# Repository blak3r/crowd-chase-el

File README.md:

## Crowd Chase EL

Is a simple EL wire controller to be used by a group of people wearing EL Wires.
Each person sets which number they are in a sequence by pressing a push button.  They also set the total number of people in their
group using the other push button.  So, if you had 3 people.  Someone would be 1 of 3, 2 of 3, and 3 of 3.

The controller then turns on their EL Wire whenever it's their turn in the sequence.

The circuit uses a basic 8 bit PIC microcontroller (sorry arduino peeps)... The board design uses all through hole components to make it easy for novices to solder.

I designed this controller for Burning Man 2013.  We all invested in some EL Wire (for safety reasons)... and thought it'd be
really cool if we blinked in succession.  Plus it'd had been a while since I had done a hardware project.

### Quick Info ###
* BOM Cost: $8.60 in Qty 10 (not including the PCBs)
* Compiler: Microchip XC8 (but any compiler for PIC16 should be fine)
* PCB Layout: Eagle v6
* License: Creative Commons Share a Like
* Microcontroller: PIC16F1826
* IDE used: MPLABX
* Battery Life: Over a week on a single CR2032.

## Where's the source code? ##
If I haven't posted it here yet, just shoot me an email (see github profile).  I reused a project that I have to strip some of the files
out of before I can release it as open source.

### Project Status ###
I'm looking for people who want to take this project to the next level.  I started this as a project for burning man 2013.
I got it to work but there are some improvements that could be made.

__I'd be willing to ship out some of the controller boards I made to someone that would like to continue this project.__

### Version 1 ###

Well, I made quite a few mistakes on the version 1 board which i'll outline here.  I had very little time to get this board
out before my deadline.  The board works it just required assembling things slightly different and in soldering a resistor
here and there to another part because there wasn't a pad.

1. I should have used optically isolated triacs!  You have to use a optically isolated triacs when you're using battery powered circuits.  Basically, you should just always
use optotriac's unless you are certain you don't need them.  If you don't, then you don't have a common ground reference between
the AC output of the inverter and the battery powered controller pcb.  This was a pretty embarrassing mistake.  I was pretty
confused how it was going to work in the first place and shouldn't have just "trusted" that the SparkFun design would work in
my situation.  The sparkfun board basically assumes that you will be powering your inverter and your controller board off one or
more DC wall worts, which in general, will share a common ground (your earth ground of your house)...

I came up with a fairly clever workaround... based around parts I had laying around.  I had some N-channel and p-channel mosfets that worked out.  I got lucky
as I added pads for a second TO-92 transistor along with .1" header to act as a breakout.  So, what I ended up doing is rather then switching the AC voltage from the invertor,
I switched the battery voltage for the inverter using a load switch.  I think this approach is actually probably better anyway as with some invertors
it's bad to keep them running without any load (ie EL Wire) connected to them.

2. The schematic has a PIC18F part on it but the target is actually a PIC16F chip.  I used an 18 pin microchip library that was in the sparkfun library but the pins
don't match 100%... so the IO pins used in the source code don't match the IO pin numbers on the schematic.

3. I forgot to put pull ups on one of the switches and it was connected to an PORTA io pin which can't have weak pullups enabled :(.

4. The voltage regulator pins didn't match the one I used in the library.  As a result you have to rotate the part slightly
 when assembling.

5. My 1.8V regulated output is NOT enough for the LEDs i picked.  The LEDs don't blink very brightly which makes
it really annoying to work with outdoors when the sun is up.

6. Some of the boards are a bit unreliable.  I found the PIC going into failsafe oscillator mode from time to time.  I'm not sure
exactly what the cause of this is... Perhaps the crystals are finicky to loading... perhaps it's the 1.8V operating voltage...
perhaps it's the fact that my boards didn't have solder mask on them and I never completely potted the boards as I ran out of
time and things shorted out.  I'd definitely recommend getting solder mask!

7. My ICSP pads for the Tag Connect didn't seem to work.  I suspect this was due to the limited number of drill sizes
that PCBExpress offers on their standard service.  The holes for the line up pins were WAY to large.  As a result, I ended up

### Other Critiques ###

1. The board could be a LOT smaller... I decided to go through-hole to make the part very easy to assemble... but it really adds a lot of bulk.
2. I wasn't very happy with the push buttons.  They take up quite a bit of board space.  I'd also like to see a switch with recessed actuators to prevent
the possibility of being pressed accidently in pocket.  Note: this didn't actually happen to us in practice... probably because of the bulky
connectors on the edges of the board.
3. Syncing is a bit difficult unless you have a group of patient people.  There were two ways to sync A) by everyone releasing a button at the same time and B) by connecting the boards
together with two wires.  The pressing a button can be difficult with a lot of people... It's hard to have everyone release the button "on 3". 1-2-3.
The wire method is also difficult when you have people who have already put their costumes on etc.

### Alternate Sync Methods ###

The way I kept the boards in sync was just by using timers in the micro and having them "reset" when the sync action occurs.  This works fairly well for
an evening or two.  Depending on where you're using it that might not be an issue.  But, getting 7 people together at Burning Man is pretty much
impossible and if you do you'll run into the issue mentioned above.  To improve the accuracy of the clocks, I used what I thought was a fairly
precise crystal and used an LDO on board to eliminate changes in the operating voltage from PIC to PIC.

What would be ideal is some sort of low power zigbee node mesh controller... where master and slaves are dynamically negotiated.  The master would then send
out a pulse signal to the slave nodes when it was their turn.  This would make the whole thing much easier to use as a group.
As people come in range they'd be assigned a position automatically.
If two people went off on their own, then they'd start blinking back and forth instead of having dead time where neither is blinking.
It would however make for some pretty complex software and increase the BOM Cost probably about $5-$10.  The possibilities
would be pretty much endless though... You could probably even do some smart algorithms to determine where people were in relation to one another.
That way you could always keep the blink pattern going from left to right even when people moved around.

A simpler approach would be a simple RF transmitter / receiver pairs.  In this topology you'd have a single master controller which would send
pulse signals to the slave boards to keep them in sync.  You can get these for about $5 but what I didn't like about that was then you
always had to have a "master" board in range of the "slave" board and they'd drain the coin cell batteries pretty fast.  The zigbee stacks have battery
friendly "time slots" in which all communications occur so the RF controllers could be off most of the time.

### Contact ####
I'm very interested in seeing this project go somewhere.  I'm afraid I don't have too much time to keep working on it nor an event
to use it at for at least a year... so send me an email if you're interested.  My email is in my github profile.

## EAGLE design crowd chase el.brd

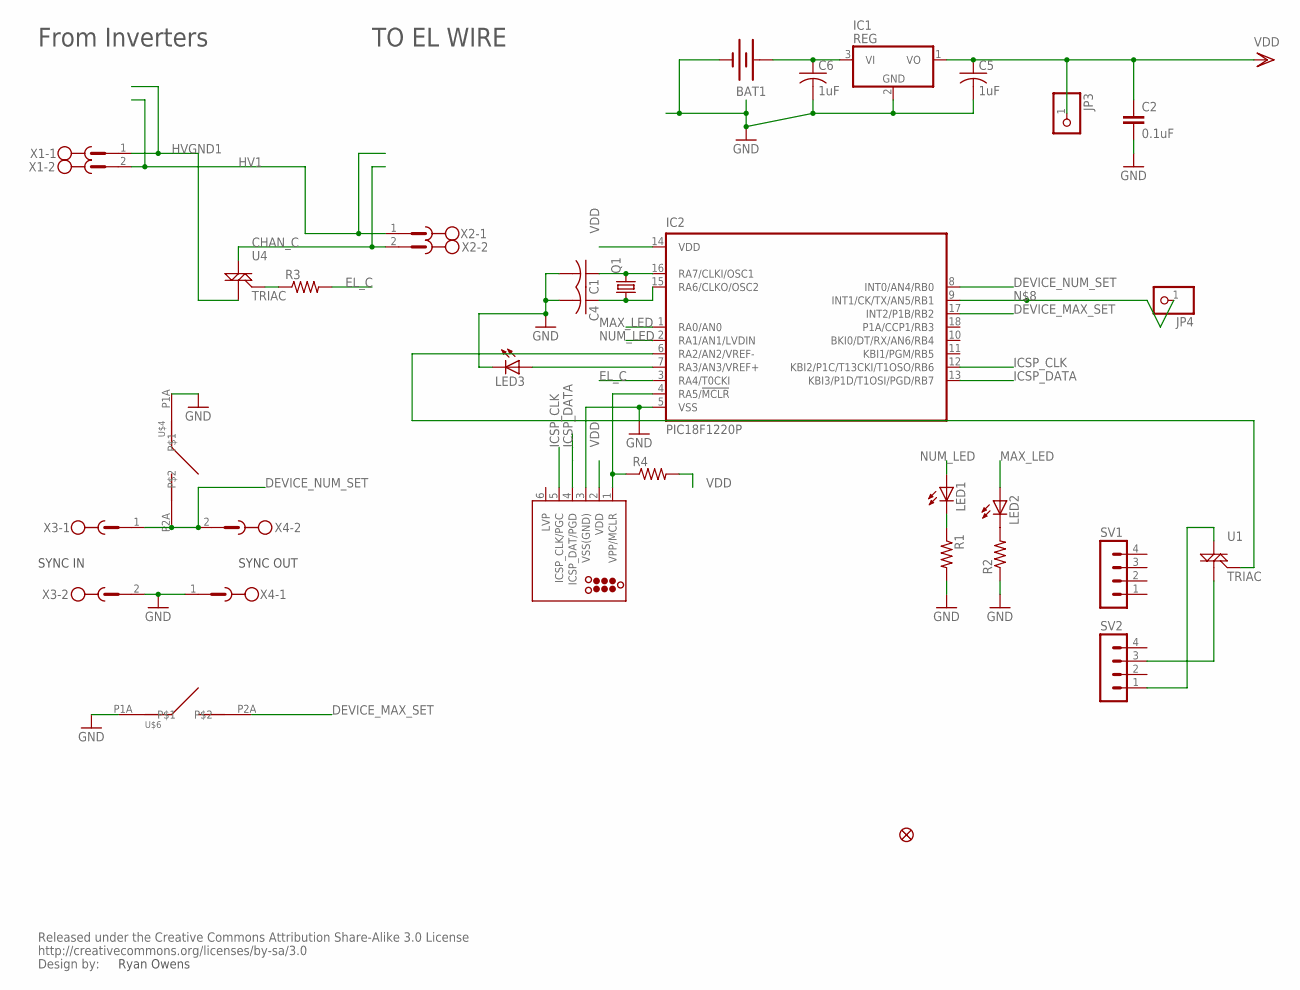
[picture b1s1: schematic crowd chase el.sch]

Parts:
BAT1: BATTERY20SMD-L; BATTCON_20MM
C1, C4: C-US025-025X050; C025-025X050
C2: 0.1uF; CAP-PTH-SMALL2
C5, C6: 1uF; C025-025X050
IC1: REG; TO92
IC2: PIC18F1220P; DIL18
J2: TC2030; TC2030-MCP-NL-CP
JP3, JP4: PINHEADER_1X1; HEADER_DIP_1X01
LED1, LED2, LED3: LED3MM
Q1: CRYSTALHC49S; HC49/S
R1, R2, R3, R4: R-US_0204/5; 0204/5
SV1, SV2: MA04-1
U1, U4: TRIAC; TO-92
U$2: FIDUCIAL1X2; FIDUCIAL-1X2
U$4, U$6: 12MMTACT_MJTP1212; MJTP1212
U$5: CREATIVE_COMMONS
X1, X2, X3, X4: MSTBV2

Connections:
CHAN_C: U4.3 (M2), X2.2
DEVICE_MAX_SET: IC2.17 (INT2/P1B/RB2), U$6.P2A
DEVICE_NUM_SET: IC2.8 (INT0/AN4/RB0), U$4.P2A, X3.1, X4.2
EL_C: IC2.3 (RA4/T0CKI), R3.2
GND: BAT1.2 (-), C1.2, C2.2, C4.2, C5.2, C6.2, IC1.2 (GND), IC2.5 (VSS), J2.3 (VSS(GND)), LED3.K (C), R1.2, R2.1, U$4.P1A, U$6.P1A, X3.2, X4.1
HV1: X1.2, X2.1
HVGND1: U4.1 (M1), X1.1
ICSP_CLK: IC2.12 (KBI2/P1C/T13CKI/T1OSO/RB6), J2.5 (ICSP_CLK/PGC)
ICSP_DATA: IC2.13 (KBI3/P1D/T1OSI/PGD/RB7), J2.4 (ICSP_DAT/PGD)
MAX_LED: IC2.1 (RA0/AN0), LED2.A
unnamed: IC2.4 (RA5/!MCLR), J2.1 (VPP/MCLR), R4.1
unnamed: C4.1, IC2.15 (RA6/CLKO/OSC2), Q1.1
unnamed: C1.1, IC2.16 (RA7/CLKI/OSC1), Q1.2
unnamed: LED1.K (C), R1.1
unnamed: LED2.K (C), R2.2
unnamed: IC2.7 (RA3/AN3/VREF+), LED3.A
unnamed: IC2.9 (INT1/CK/TX/AN5/RB1), JP4.1
unnamed: BAT1.3 (+), C6.1, IC1.3 (VI)
unnamed: R3.1, U4.2 (G)
unnamed: SV2.1, U1.3 (M2)
unnamed: SV2.3, U1.1 (M1)
unnamed: IC2.6 (RA2/AN2/VREF-), U1.2 (G)
NUM_LED: IC2.2 (RA1/AN1/LVDIN), LED1.A
VDD: C2.1, C5.1, IC1.1 (VO), IC2.14 (VDD), J2.2 (VDD), JP3.1, R4.2

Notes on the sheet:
Ryan Owens
TO EL WIRE
From Inverters
SYNC OUT
SYNC IN

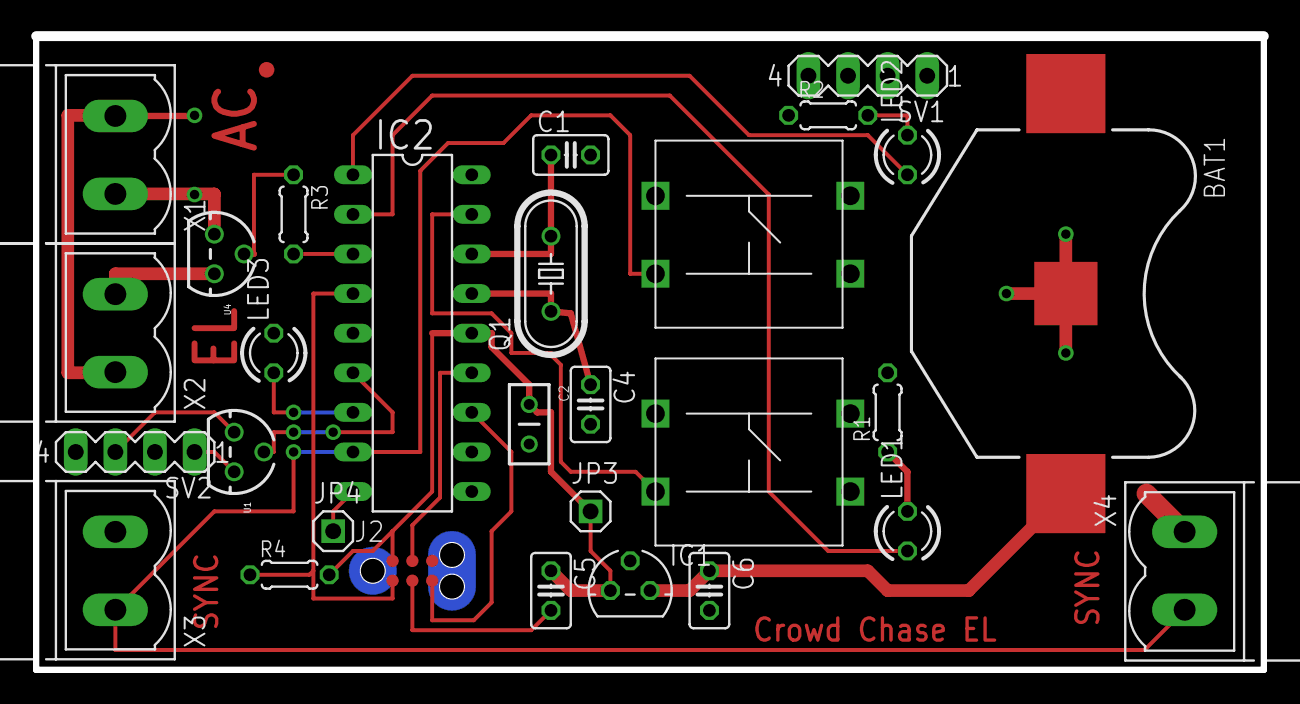
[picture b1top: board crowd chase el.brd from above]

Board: 2 copper layers, 78.7 x 40.5 mm, 31 parts (0 on the bottom side), 24 nets.

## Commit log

2013-08-19 Initial placement
2013-08-19 No more airwires
2013-08-19 v1.0 -- Fabbed Version
2013-09-05 updated readme with version 1 details.
2013-09-05 formatting fixes in readme

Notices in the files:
parts and their libraries:
SparkFun: Released under the Creative Commons Attribution Share-Alike 3.0 License
SparkFun: http://creativecommons.org/licenses/by-sa/3.0
tag-connect: ©2009 ROFA.cz - modified and updated by Robert Darlington ‹rdarlington@gmail.com›
